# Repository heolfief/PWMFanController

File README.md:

# PWMFanController
This is a simple AVR based PWM PC fan controller.

The MCU is an ATtiny85.

Software in interrupt-driven. A potentiometer value is read by the ADC and then used to set the duty-cycle of a 8bits PWM, driving the fan's speed.

The board is small (33x15mm) and is designed to be directly attached to a standard potentiometer.

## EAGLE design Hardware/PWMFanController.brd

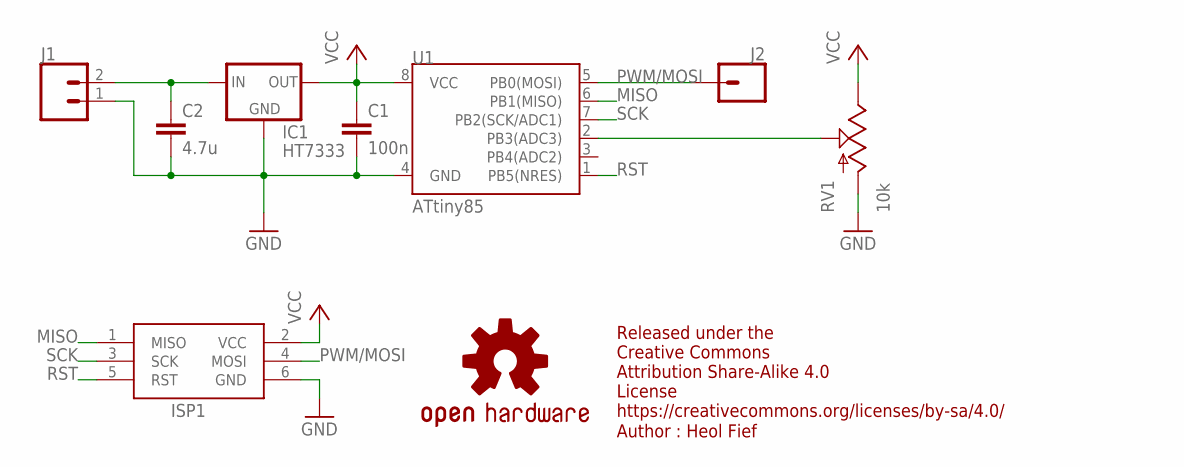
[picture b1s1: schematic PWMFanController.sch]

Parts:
C1: 100n; C0805K
C2: 4.7u; C0805K
IC1: HT7333; SOT-89
ISP1: AVRISP-6; AVRISP
J1: CONN_02; 1X02
J2: CONN_01; 1X01
LOGO1: OSHW-LOGOS-COPPER; OSHW-LOGO-S_COPPER
RV1: 10k; POT_MAMMOTH
U1: ATtiny85; SO08-EIAJ_MCU

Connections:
GND: C1.2, C2.2, IC1.2 (GND), ISP1.6 (GND), J1.1, RV1.P$1 (A), U1.4 (GND)
MISO: ISP1.1 (MISO), U1.6 (PB1(MISO))
unnamed: C2.1, IC1.3 (IN), IC1.4 (IN), J1.2
unnamed: RV1.P$2 (S), U1.2 (PB3(ADC3))
PWM/MOSI: ISP1.4 (MOSI), J2.1, U1.5 (PB0(MOSI))
RST: ISP1.5 (RST), U1.1 (PB5(NRES))
SCK: ISP1.3 (SCK), U1.7 (PB2(SCK/ADC1))
VCC: C1.1, IC1.1 (OUT), ISP1.2 (VCC), RV1.P$3 (E), U1.8 (VCC)

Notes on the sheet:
Released under the Creative Commons Attribution Share-Alike 4.0 License https://creativecommons.org/licenses/by-sa/4.0/
Author : Heol Fief

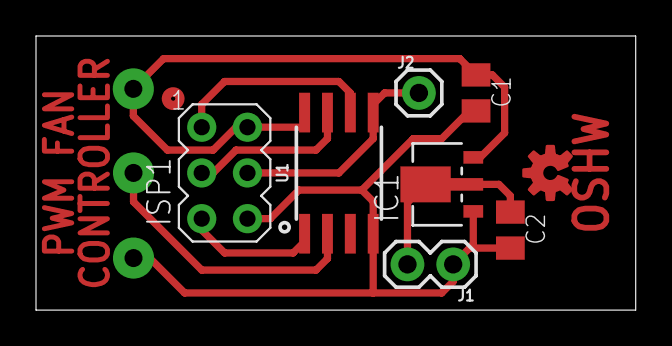
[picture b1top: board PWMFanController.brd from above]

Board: 2 copper layers, 33.3 x 15.2 mm, 9 parts (0 on the bottom side), 8 nets.

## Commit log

2017-08-16 Create newfolder
2017-08-16 Update main.c
    Edit header
2017-08-17 Add Eagle files
2017-08-17 Update .editorconfig
    Modify tab width
2017-08-30 Add layout
    Add ready to print PDF layout for toner tranfer
2017-09-02 Add Hardware documentation
2017-09-02 Add author mention

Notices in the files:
parts and their libraries:
SparkFun-Connectors: Licensing: Creative Commons ShareAlike 4.0 International - https://creativecommons.org/licenses/by-sa/4.0
